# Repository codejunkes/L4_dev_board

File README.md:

# L4_dev_board
Development board for ultra-low power applications

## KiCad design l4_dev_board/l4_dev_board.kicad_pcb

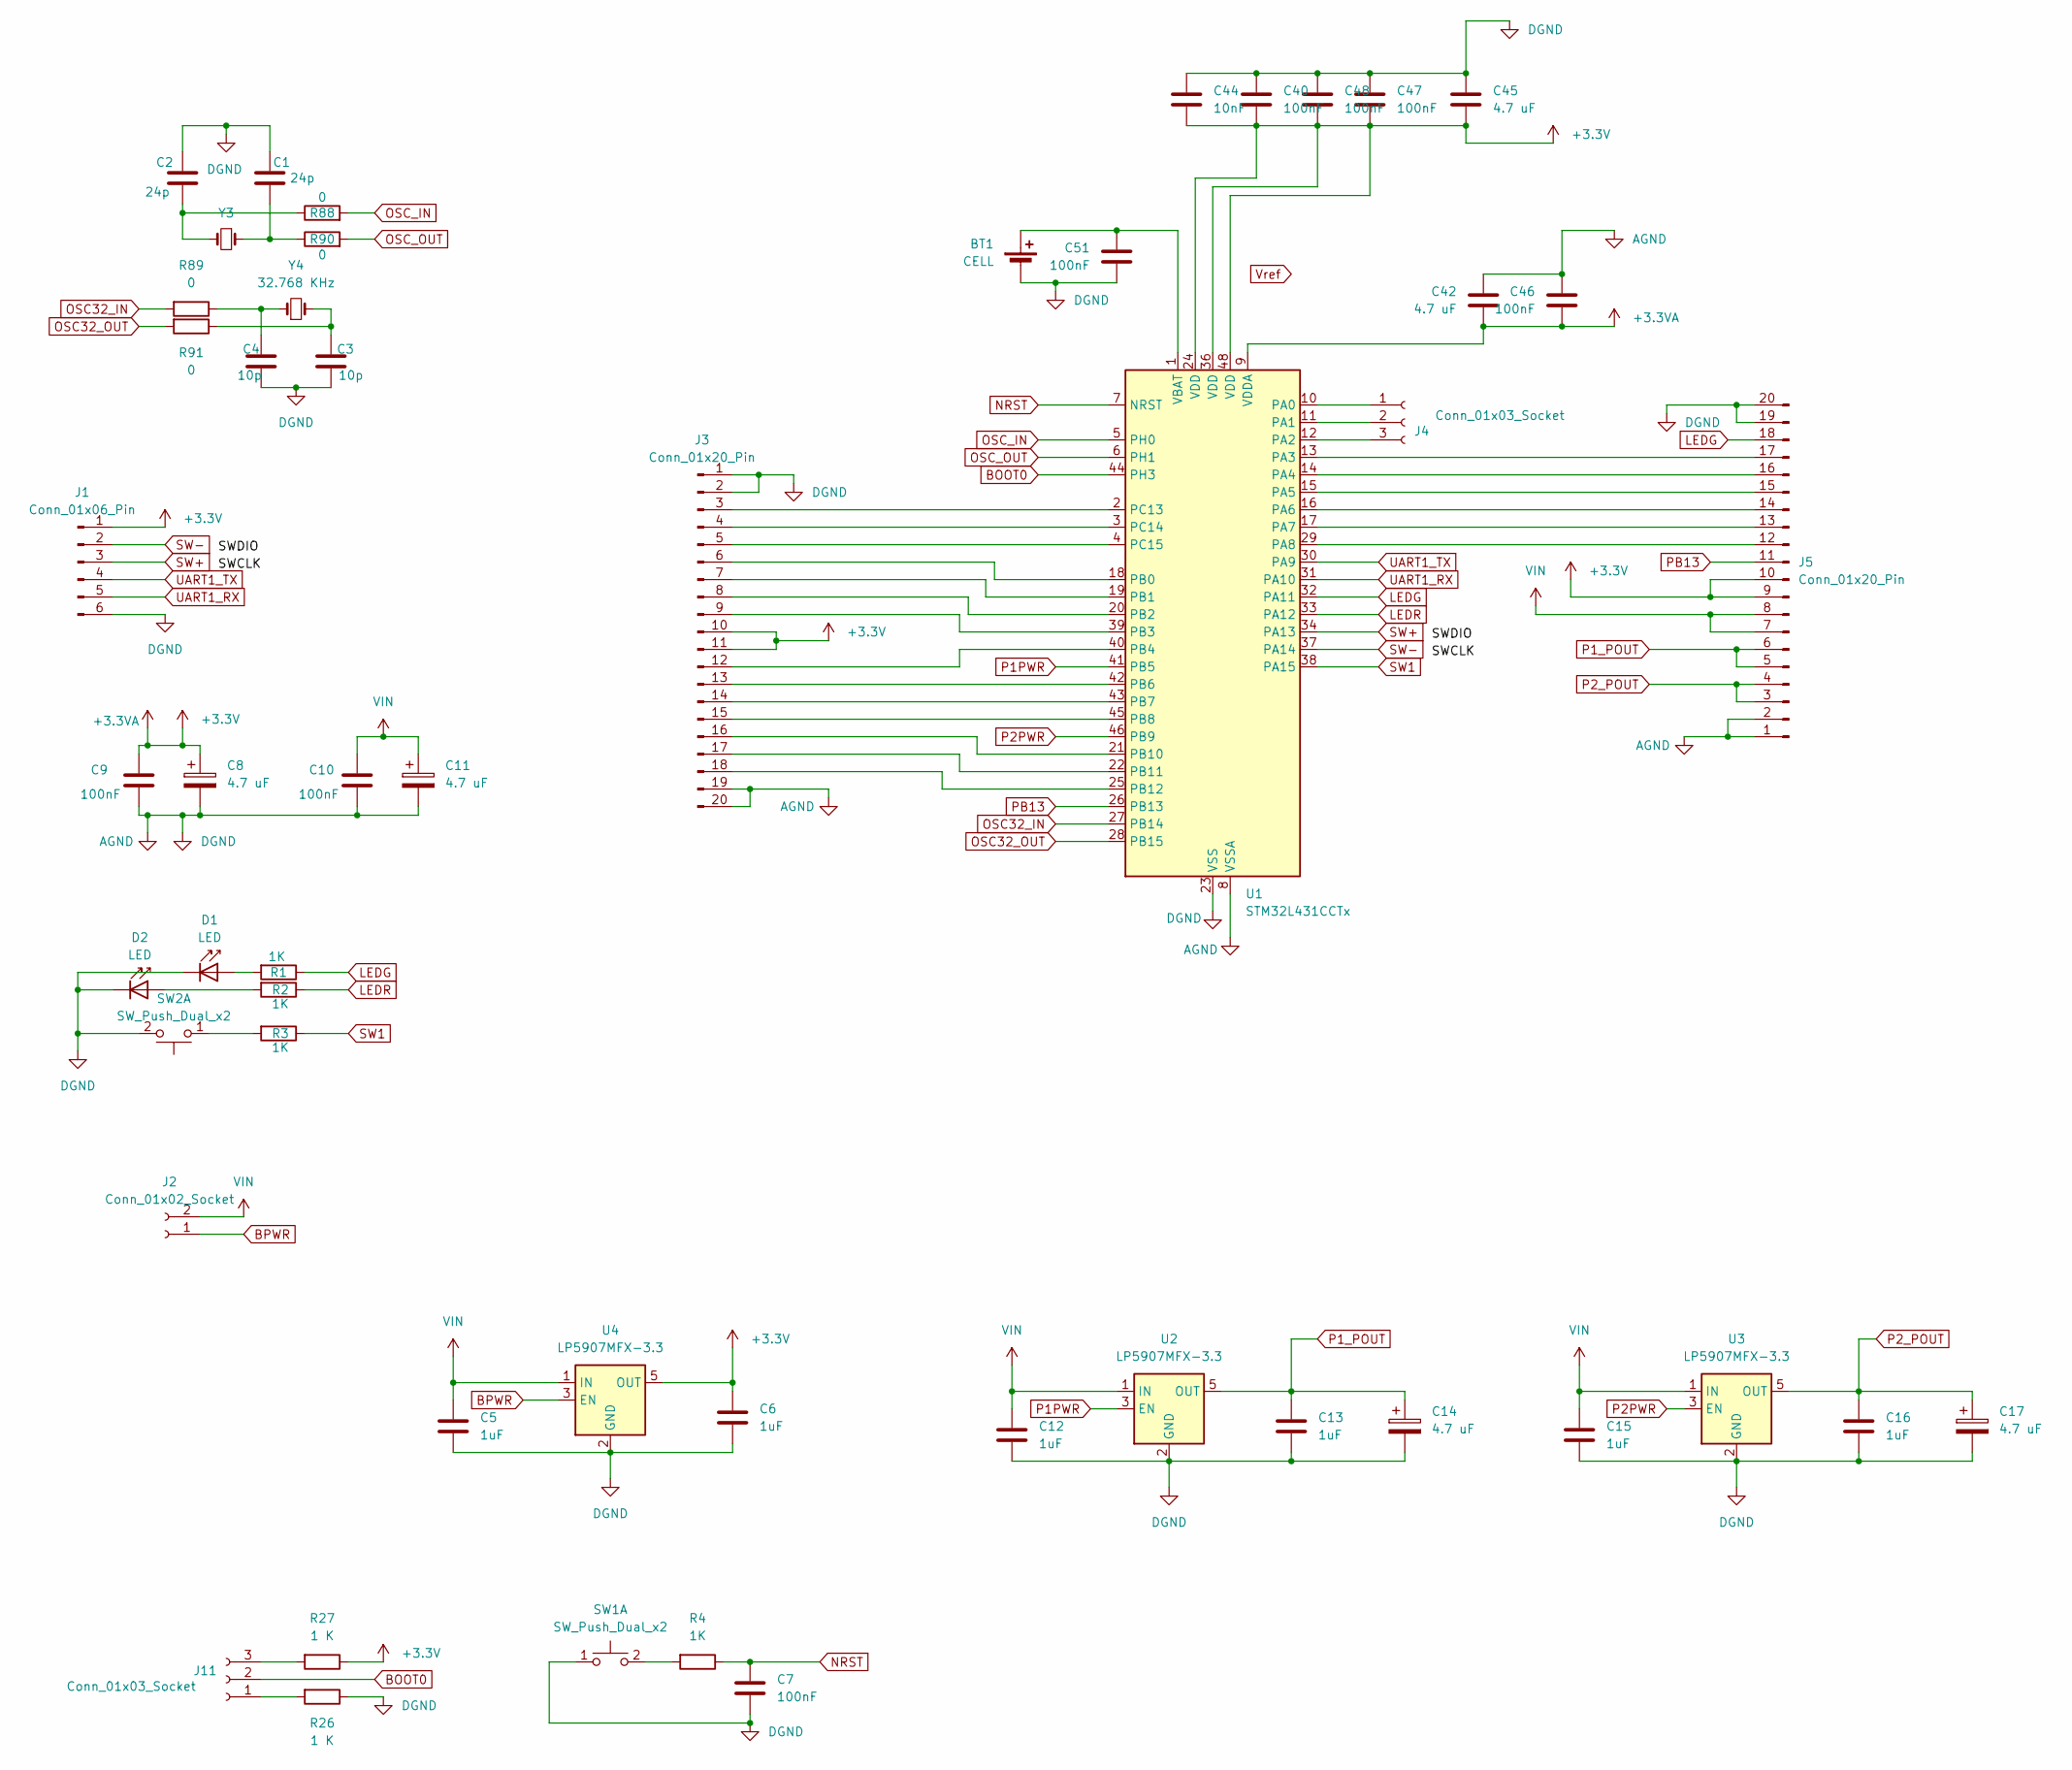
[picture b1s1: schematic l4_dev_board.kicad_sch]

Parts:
BT1: CELL; BatteryHolder_Keystone_1060_1x2032
C1, C2: 24p; C_0603_1608Metric_Pad1.08x0.95mm_HandSolder
C3, C4: 10p; C_0603_1608Metric_Pad1.08x0.95mm_HandSolder
C5, C6, C12, C13, C15, C16: 1uF; C_0603_1608Metric_Pad1.08x0.95mm_HandSolder
C7, C9, C10, C40, C46, C47, C48, C51: 100nF; C_0603_1608Metric_Pad1.08x0.95mm_HandSolder
C8, C11, C14, C17: 4.7 uF; CP_Radial_D8.0mm_P2.50mm
C42, C45: 4.7 uF; C_0603_1608Metric_Pad1.08x0.95mm_HandSolder
C44: 10nF; C_0603_1608Metric_Pad1.08x0.95mm_HandSolder
D1, D2: LED; LED_0603_1608Metric_Pad1.05x0.95mm_HandSolder
J1: Conn_01x06_Pin; PinSocket_1x06_P2.54mm_Vertical
J2: Conn_01x02_Socket; PinHeader_1x02_P2.54mm_Vertical
J3, J5: Conn_01x20_Pin; PinHeader_2x10_P2.54mm_Vertical
J4, J11: Conn_01x03_Socket; PinHeader_1x03_P2.54mm_Vertical
R1, R2, R3, R4: 1K; R_0603_1608Metric_Pad0.98x0.95mm_HandSolder
R26, R27: 1 K; R_0603_1608Metric_Pad0.98x0.95mm_HandSolder
R88, R89, R90, R91: 0; R_0603_1608Metric_Pad0.98x0.95mm_HandSolder
SW1, SW2: SW_Push_Dual_x2; SW_Push_SPST_NO_Alps_SKRK
U1: STM32L431CCTx; LQFP-48_7x7mm_P0.5mm
U2, U3, U4: LP5907MFX-3.3; SOT-23-5
Y3: 10 MHz; Crystal_HC18-U_Vertical
Y4: 32.768 KHz; Crystal_DS26_D2.0mm_L6.0mm_Horizontal_1EP_style1

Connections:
+3.3V: C6.1, C8.1, C9.1, C40.2, C42.2, C44.2, C45.2, C46.2, C47.2, C48.2, J1.1, J3.10, J3.11, J5.9, J5.10, R27.1, U1.9 (VDDA), U1.24 (VDD), U1.36 (VDD), U1.48 (VDD), U4.5 (OUT)
AGND: BT1.2 (-), C1.2, C2.2, C3.2, C4.2, C5.2, C6.2, C7.2, C8.2, C9.2, C10.2, C11.2, C12.2, C13.2, C14.2, C15.2, C16.2, C17.2, C40.1, C42.1, C44.1, C45.1, C46.1, C47.1, C48.1, C51.2, D1.1 (K), D2.1 (K), J1.6, J3.1, J3.2, J3.19, J3.20, J5.1, J5.2, J5.19, J5.20, R26.1, SW1.1 (C), SW2.2 (D), U1.8 (VSSA), U1.23 (VSS), U1.35 (VSS), U1.47 (VSS), U2.2 (GND), U3.2 (GND), U4.2 (GND)
BOOT0: J11.2, U1.44 (PH3)
BPWR: J2.1, U4.3 (EN)
LEDG: J5.18, R1.1, U1.32 (PA11)
LEDR: R2.1, U1.33 (PA12)
NRST: C7.1, R4.1, U1.7 (NRST)
unnamed: BT1.1 (+), C51.1, U1.1 (VBAT)
unnamed: C1.1, R90.1, Y3.1
unnamed: C2.1, R88.1, Y3.2
unnamed: C3.1, R91.1, Y4.2
unnamed: C4.1, R89.1, Y4.1
unnamed: D1.2 (A), R1.2
unnamed: D2.2 (A), R2.2
unnamed: J3.3, U1.2 (PC13)
unnamed: J3.4, U1.3 (PC14)
unnamed: J3.5, U1.4 (PC15)
unnamed: J3.6, U1.18 (PB0)
unnamed: J3.7, U1.19 (PB1)
unnamed: J3.8, U1.20 (PB2)
unnamed: J3.9, U1.39 (PB3)
unnamed: J3.12, U1.40 (PB4)
unnamed: J3.13, U1.42 (PB6)
unnamed: J3.14, U1.43 (PB7)
unnamed: J3.15, U1.45 (PB8)
unnamed: J3.16, U1.21 (PB10)
unnamed: J3.17, U1.22 (PB11)
unnamed: J3.18, U1.25 (PB12)
unnamed: J4.1, U1.10 (PA0)
unnamed: J4.2, U1.11 (PA1)
unnamed: J4.3, U1.12 (PA2)
unnamed: J5.12, U1.29 (PA8)
unnamed: J5.13, U1.17 (PA7)
unnamed: J5.14, U1.16 (PA6)
unnamed: J5.15, U1.15 (PA5)
unnamed: J5.16, U1.14 (PA4)
unnamed: J5.17, U1.13 (PA3)
unnamed: J11.1, R26.2
unnamed: J11.3, R27.2
unnamed: R4.2, SW1.2 (D)
unnamed: R3.2, SW2.1 (C)
OSC32_IN: R89.2, U1.27 (PB14)
OSC32_OUT: R91.2, U1.28 (PB15)
OSC_IN: R88.2, U1.5 (PH0)
OSC_OUT: R90.2, U1.6 (PH1)
P1PWR: U1.41 (PB5), U2.3 (EN)
P1_POUT: C13.1, C14.1, J5.5, J5.6, U2.5 (OUT)
P2PWR: U1.46 (PB9), U3.3 (EN)
P2_POUT: C16.1, C17.1, J5.3, J5.4, U3.5 (OUT)
PB13: J5.11, U1.26 (PB13)
SW1: R3.1, U1.38 (PA15)
SW+: J1.3, U1.34 (PA13)
SW-: J1.2, U1.37 (PA14)
UART1_RX: J1.5, U1.31 (PA10)
UART1_TX: J1.4, U1.30 (PA9)
VIN: C5.1, C10.1, C11.1, C12.1, C15.1, J2.2, J5.7, J5.8, U2.1 (IN), U3.1 (IN), U4.1 (IN)

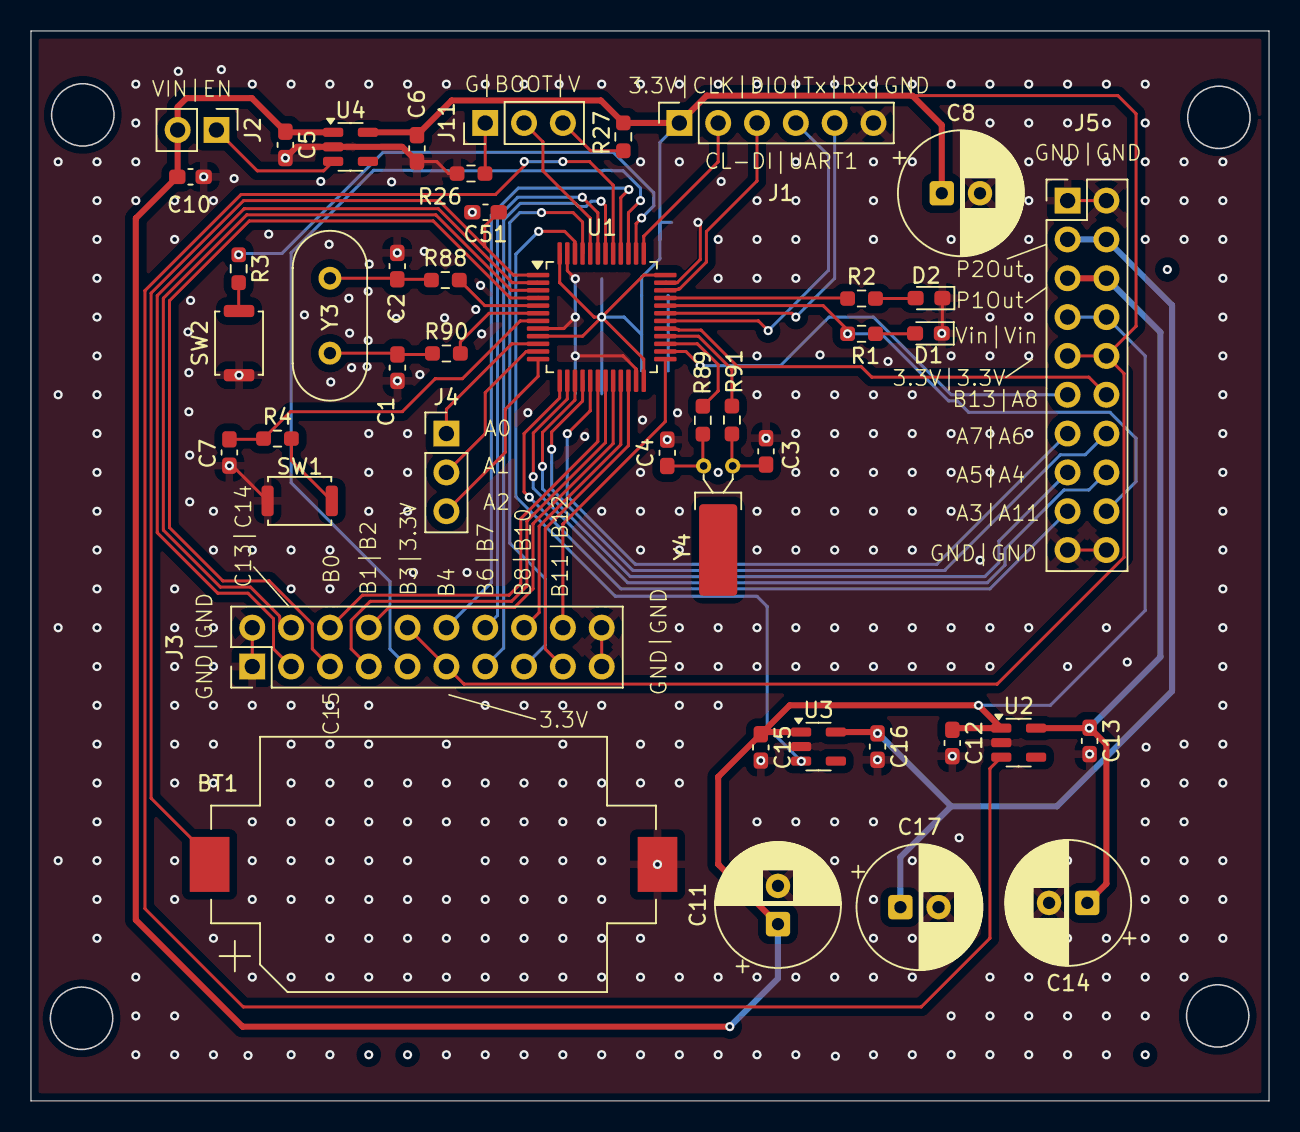
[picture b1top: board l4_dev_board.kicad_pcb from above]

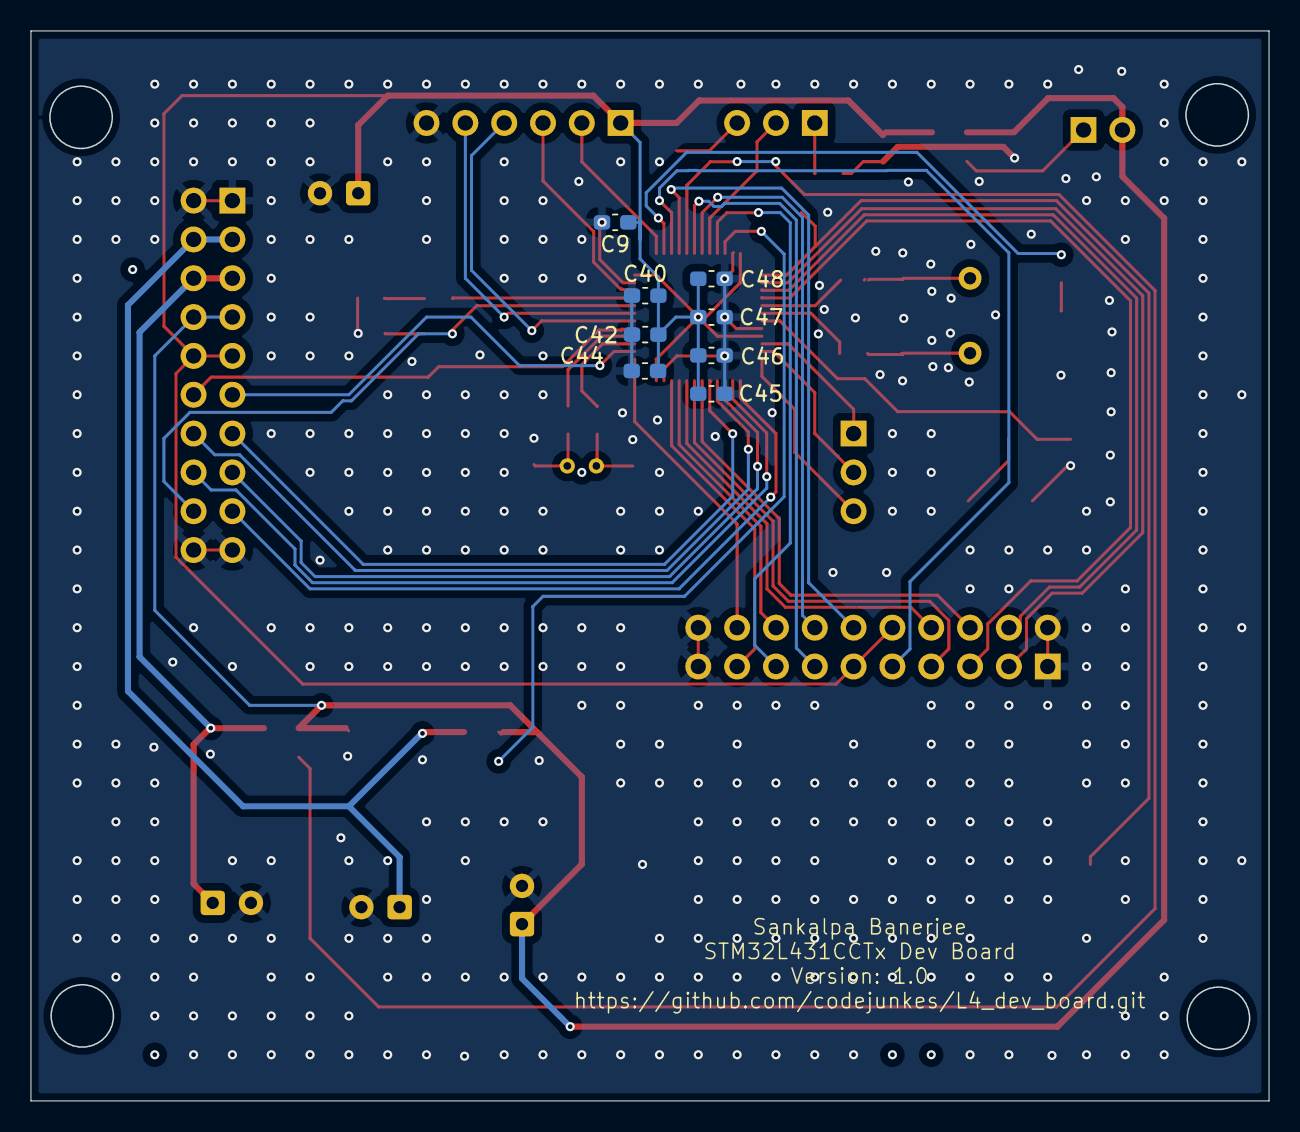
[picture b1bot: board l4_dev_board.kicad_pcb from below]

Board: 2 copper layers, 80.9 x 70.0 mm, 52 parts (8 on the bottom side), 56 nets.

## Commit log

2025-09-21 Create Hardware
2025-09-21 Hardware Schematic, garber and KiCAD files added.
2025-09-21 documents and manual added
2025-09-21 STM32IDE files for L4 Dev board.
    Only implemented deep sleep and wake from sleep using the internal RTC clock (32KHz).
